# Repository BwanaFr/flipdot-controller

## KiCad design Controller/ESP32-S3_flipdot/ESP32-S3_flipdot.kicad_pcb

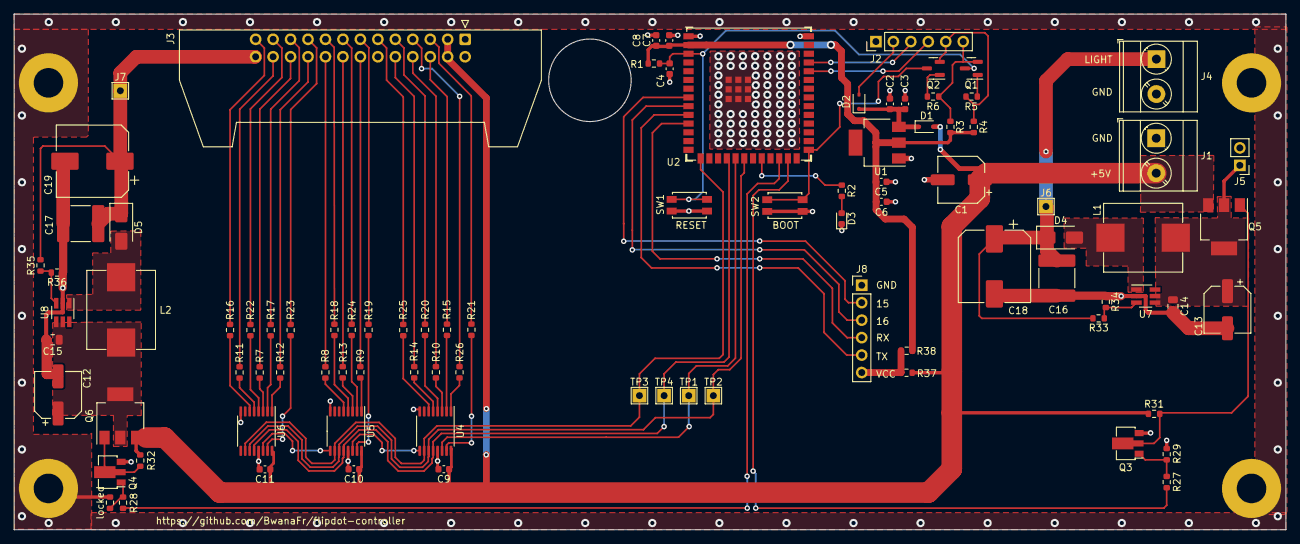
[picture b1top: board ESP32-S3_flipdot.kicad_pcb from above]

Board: 2 copper layers, 185.0 x 75.0 mm, 95 parts (0 on the bottom side), 80 nets.

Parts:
C1, C12, C13: 220uF; CP_Elec_6.3x7.7
C2, C6, C8: 10uF; C_0603_1608Metric
C3, C5, C7, C9, C10, C11: 100nF; C_0603_1608Metric
C4: 1uF; C_0603_1608Metric
C14, C15: 22uF; C_0805_2012Metric
C16, C17: 22uF; C_2220_5750Metric
C18, C19: 220uF; CP_Elec_10x10
D1, D2: 1N5819WS; D_SOD-323
D3: LED; LED_0603_1608Metric
D4, D5: SS34; D_SMA
H1, H2, H3, H4: MountingHole_Pad; MountingHole_4.3mm_M4_Pad
J1: Power in; TerminalBlock_Phoenix_MKDS-3-2-5.08_1x02_P5.08mm_Horizontal
J2: FTDI; PinHeader_1x06_P2.54mm_Vertical
J3: Mobitec display; IDC-Header_2x13_P2.54mm_Latch_Horizontal
J4: BackLight; TerminalBlock_Phoenix_MKDS-3-2-5.08_1x02_P5.08mm_Horizontal
J5: BL_CMD; PinHeader_1x02_P2.54mm_Vertical
J6: BL_PWR; TestPoint_THTPad_2.0x2.0mm_Drill1.0mm
J7: COIL_PWR; TestPoint_THTPad_2.0x2.0mm_Drill1.0mm
J8: Aux_conn; PinHeader_1x06_P2.54mm_Vertical
L1, L2: 22uH; YSPI1050-220M
Q1, Q2: BC817; SOT-23
Q3, Q4: 2N3904; SOT-89-3
Q5, Q6: ZXMP4A16G; SOT-223-3_TabPin2
R1, R3, R4, R5, R6: 10k; R_0603_1608Metric
R2: 2k; R_0603_1608Metric
R7, R8, R9, R10, R11, R12, R13, R14, R15, R16, R17, R18, R19, R20, R21, R22, R23, R24, R25, R26: 100; R_0603_1608Metric
R27, R28: 330; R_0603_1608Metric
R29, R31, R32: 4.7k; R_0603_1608Metric
R33: 75k; R_0603_1608Metric
R34, R36: 2.2k; R_0603_1608Metric
R35: 78.7k; R_0603_1608Metric
R37, R38: 0; R_0603_1608Metric
SW1: Reset; SW_SPST_EVQP2
SW2: Boot; SW_SPST_EVQP2
TP1, TP2, TP3, TP4: TestPoint; TestPoint_THTPad_2.0x2.0mm_Drill1.0mm
U1: LM1117MP-3.3; SOT-223
U2: ESP32-S3-WROOM-1U-N16R8; ESP32-S3-WROOM-1U
U4, U5, U6: 74HCT595; TSSOP-16_4.4x5mm_P0.65mm
U7, U8: MT3608; SOT-23-6_Handsoldering
locked: 4.7k; R_0603_1608Metric

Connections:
+3V3: C5.1, C6.1, C7.1, C8.1, R1.1, R3.2, R4.2, R38.1, U1.2 (VO), U2.2 (3V3)
+5V: C1.1, C9.1, C10.1, C11.1, D1.2 (A), J1.2, J3.3, J3.4, Q5.3 (S), Q6.3 (S), R31.1, R32.1, R37.1, U4.16 (VCC), U5.16 (VCC), U6.16 (VCC)
+5VP: C2.1, C3.1, D1.1 (K), D2.1 (K), U1.3 (VI)
/BACKLIGHT_ON: R27.1, U2.25 (GPIO48/SPICLK_N/SUBSPICLK_N_DIFF)
/COILS_EN: R28.1, U2.24 (GPIO47/SPICLK_P/SUBSPICLK_P_DIFF)
/DC-DC Step-up/+5V_BL: C13.1, C14.1, J5.1, L1.1, Q5.2 (D), U7.4 (EN), U7.5 (IN)
/ESP32/CHIP_PU: C4.1, Q1.3 (C), R1.2, SW1.2, U2.3 (EN)
/ESP32/DTR: J2.5, Q2.2 (E), R4.1, R5.1
/ESP32/GPIO0: Q2.3 (C), SW2.2, U2.27 (GPIO0/BOOT)
/ESP32/GPIO15: J8.2, U2.8 (GPIO15/U0RTS/ADC2_CH4/XTAL_32K_P)
/ESP32/GPIO16: J8.3, U2.9 (GPIO16/U0CTS/ADC2_CH5/XTAL_32K_N)
/ESP32/RTS: J2.6, Q1.2 (E), R3.1, R6.1
/ESP32/U0RXD: J2.4, U2.36 (U0RXD/GPIO44/CLK_OUT2)
/ESP32/U0TXD: J2.3, U2.37 (U0TXD/GPIO43/CLK_OUT1)
/ESP32/U1RXD: J8.4, U2.11 (GPIO18/U1RXD/ADC2_CH7/CLK_OUT3)
/ESP32/U1TXD: J8.5, U2.10 (GPIO17/U1TXD/ADC2_CH6)
/Outputs/B~W: R8.1, U5.5 (QF)
/Outputs/C0: R19.2, U5.15 (QA)
/Outputs/C1: R9.1, U5.1 (QB)
/Outputs/C2: R24.2, U5.2 (QC)
/Outputs/C3: R13.1, U5.3 (QD)
/Outputs/C4: R18.2, U5.4 (QE)
/Outputs/P0: R23.2, U6.15 (QA)
/Outputs/P1: R12.1, U6.1 (QB)
/Outputs/P2: R17.2, U6.2 (QC)
/Outputs/P3: R7.1, U6.3 (QD)
/Outputs/P4: R22.2, U6.4 (QE)
/Outputs/P5: R11.1, U6.5 (QF)
/Outputs/P6: R16.2, U6.6 (QG)
/Outputs/R0: R21.2, U4.15 (QA)
/Outputs/R1: R26.2, U4.1 (QB)
/Outputs/R2: R15.1, U4.2 (QC)
/Outputs/R3: R10.1, U4.3 (QD)
/Outputs/R4: R20.2, U4.4 (QE)
/Outputs/R5: R14.1, U4.5 (QF)
/Outputs/R6: R25.2, U4.6 (QG)
/Outputs/RCLK: TP4.1, U2.18 (GPIO10/TOUCH10/ADC1_CH9/FSPICS0/FSPIIO4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), U4.12 (RCLK), U5.12 (RCLK), U6.12 (RCLK)
/Outputs/SER: TP1.1, U2.19 (GPIO11/TOUCH11/ADC2_CH0/FSPID/FSPIIO5/S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), U4.14 (SER)
/Outputs/SRCLK: TP2.1, U2.20 (GPIO12/TOUCH12/ADC2_CH1/FSPICLK/FSPIIO6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), U4.11 (SRCLK), U5.11 (SRCLK), U6.11 (SRCLK)
/Outputs/~SRCLR: TP3.1, U2.15 (GPIO3/TOUCH3/ADC1_CH2), U4.10 (~SRCLR), U5.10 (~SRCLR), U6.10 (~SRCLR)
GND: C1.2, C2.2, C3.2, C4.2, C5.2, C6.2, C7.2, C8.2, C9.2, C10.2, C11.2, C12.2, C13.2, C14.2, C15.2, C16.2, C17.2, C18.2, C19.2, D3.1 (K), H1.1, H2.1, H3.1, H4.1, J1.1, J2.1, J3.1, J3.2, J4.2, J5.2, J8.1, Q3.3 (E), Q4.3 (E), R29.2, R34.2, R36.2, SW1.1, SW2.1, U1.1 (GND), U2.1 (GND), U2.40 (GND), U2.41 (GND), U4.8 (GND), U4.13 (~OE), U5.8 (GND), U5.13 (~OE), U6.8 (GND), U6.13 (~OE), U7.2 (GND), U8.2 (GND), locked.2
unnamed: D2.2 (A), J2.2
unnamed: D3.2 (A), R2.2
unnamed: D4.2 (A), L1.2, U7.1 (SW)
unnamed: C16.1, C18.1, D4.1 (K), J4.1, J6.1, R33.1
unnamed: D5.2 (A), L2.2, U8.1 (SW)
unnamed: J3.5, R21.1
unnamed: J3.6, R15.2
unnamed: J3.7, R26.1
unnamed: J3.8, R10.2
unnamed: J3.9, R20.1
unnamed: J3.10, R14.2
unnamed: J3.11, R25.1
unnamed: J3.13, R19.1
unnamed: J3.14, R9.2
unnamed: J3.15, R24.1
unnamed: J3.16, R13.2
unnamed: J3.17, R18.1
unnamed: J3.18, R8.2
unnamed: J3.19, R23.1
unnamed: J3.20, R12.2
unnamed: J3.21, R17.1
unnamed: J3.22, R7.2
unnamed: J3.23, R22.1
unnamed: J3.24, R11.2
unnamed: J3.25, R16.1
unnamed: J8.6, R37.2, R38.2
unnamed: Q1.1 (B), R5.2
unnamed: Q2.1 (B), R6.2
unnamed: Q3.1 (B), R27.2, R29.1
unnamed: Q3.2 (C), Q5.1 (G), R31.2
unnamed: Q4.1 (B), R28.2, locked.1
unnamed: Q4.2 (C), Q6.1 (G), R32.2
unnamed: C12.1, C15.1, L2.1, Q6.2 (D), U8.4 (EN), U8.5 (IN)
unnamed: R2.1, U2.22 (GPIO14/TOUCH14/ADC2_CH3/FSPIWP/FSPIDQS/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)
unnamed: U4.9 (QH'), U5.14 (SER)
unnamed: U5.9 (QH'), U6.14 (SER)
unnamed: R33.2, R34.1, U7.3 (FB)
unnamed: R35.2, R36.1, U8.3 (FB)
Vdrive: C17.1, C19.1, D5.1 (K), J3.26, J7.1, R35.1

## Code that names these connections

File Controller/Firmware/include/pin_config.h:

#ifndef _PIN_CONFIG__
#define _PIN_CONFIG__

#include <SPI.h>

//SPI pins for shift registers
#define SER MOSI
#define SRCLK SCK
#define RCLK SS
#define SRCLR 3
//Coil DC/DC control
#define COIL 47
//Backlight DC/DC control
#define BACKLIGHT 48
//Onboard LED
#define LED 14

#endif

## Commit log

2023-10-16 Fond ok
2023-10-16 Support ESP32
2023-10-16 Before PSU
2023-10-16 PSU Ok
2023-10-17 Added burndy
2023-10-17 First print
2023-10-23 Working on firmware
2023-10-23 Fixed OTA
2023-10-26 No double-buffering of communication
2023-12-05 WIP on PCB
2023-12-05 Before new dc-dc
2023-12-06 Trivial firmware to test IO
2023-12-07 PCB in production!
2023-12-22 Progress on controller firmware
